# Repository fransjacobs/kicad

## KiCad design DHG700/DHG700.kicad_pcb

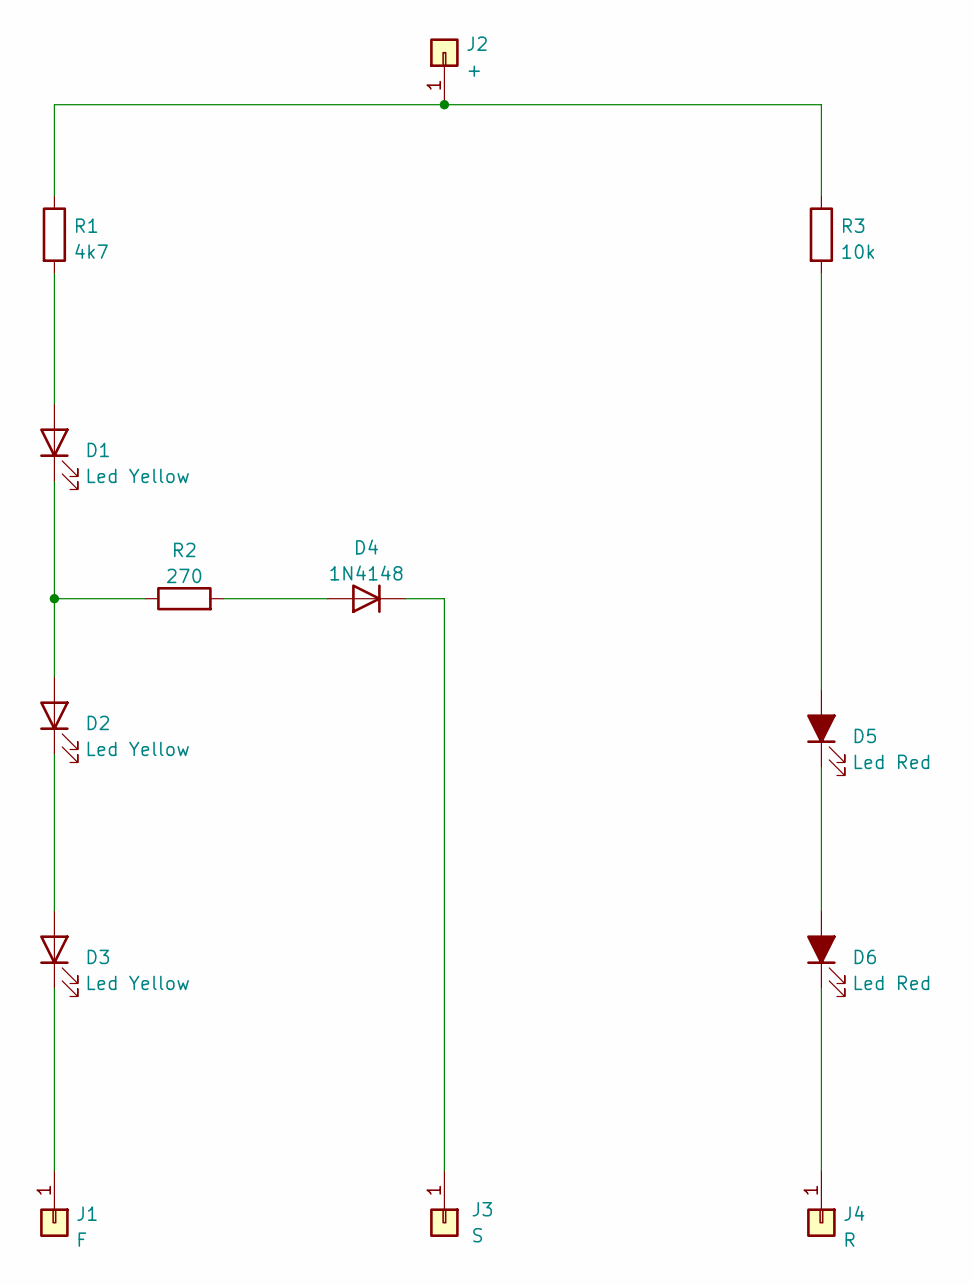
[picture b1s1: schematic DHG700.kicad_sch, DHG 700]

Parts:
D1, D2, D3: Led Yellow; LED_0603_1608Metric
D4: 1N4148; D_DO-35_SOD27_P7.62mm_Horizontal
D5, D6: Led Red; LED_0603_1608Metric
J1: F; SolderWirePad_1x01_SMD_1x2mm
J2: +; SolderWirePad_1x01_SMD_1x2mm
J3: S; SolderWirePad_1x01_SMD_1x2mm
J4: R; SolderWirePad_1x01_SMD_1x2mm
R1: 4k7; R_1206_3216Metric
R2: 270; R_1206_3216Metric
R3: 10k; R_1206_3216Metric

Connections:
unnamed: D1.1 (K), D2.2 (A), R2.1
unnamed: D1.2 (A), R1.2
unnamed: D2.1 (K), D3.2 (A)
unnamed: D3.1 (K), J1.1
unnamed: D4.1 (K), J3.1
unnamed: D4.2 (A), R2.2
unnamed: D5.1 (K), D6.2 (A)
unnamed: D5.2 (A), R3.2
unnamed: D6.1 (K), J4.1
unnamed: J2.1, R1.1, R3.1

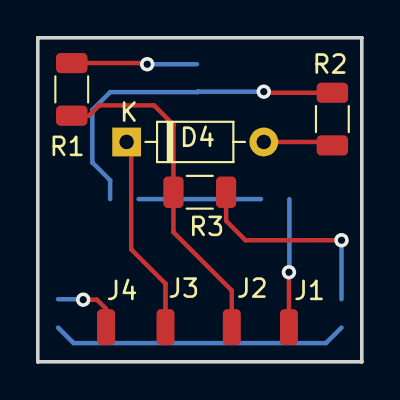
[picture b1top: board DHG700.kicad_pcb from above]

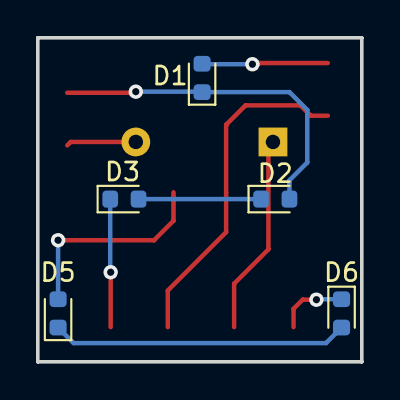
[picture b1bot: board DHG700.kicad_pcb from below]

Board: 2 copper layers, 18.0 x 18.0 mm, 13 parts (5 on the bottom side), 10 nets.

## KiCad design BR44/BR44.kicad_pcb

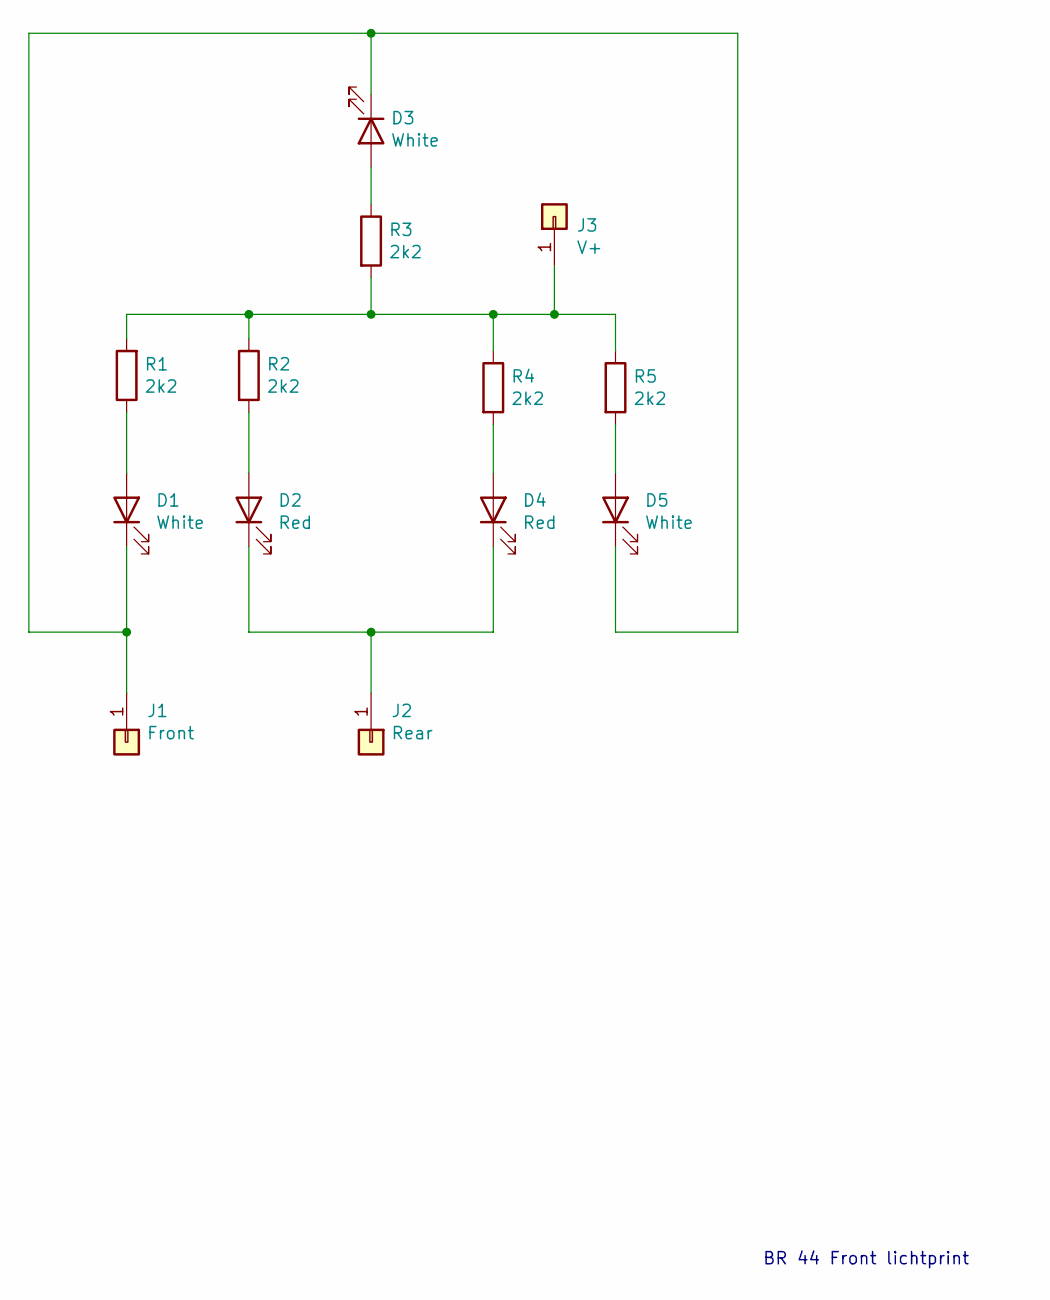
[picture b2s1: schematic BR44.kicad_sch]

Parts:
D1, D3, D5: White; LED_1206_3216Metric_Pad1.42x1.75mm_HandSolder
D2, D4: Red; LED_1206_3216Metric_Pad1.42x1.75mm_HandSolder
J1: Front; TestPoint_Keystone_5019_Minature
J2: Rear; TestPoint_Keystone_5019_Minature
J3: V+; TestPoint_Keystone_5019_Minature
R1, R2, R3, R4, R5: 2k2; R_1206_3216Metric

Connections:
unnamed: D1.1 (K), D3.1 (K), D5.1 (K), J1.1
unnamed: D1.2 (A), R1.1
unnamed: D2.1 (K), D4.1 (K), J2.1
unnamed: D2.2 (A), R2.2
unnamed: D3.2 (A), R3.1
unnamed: D4.2 (A), R4.2
unnamed: D5.2 (A), R5.2
unnamed: J3.1, R1.2, R2.1, R3.2, R4.1, R5.1

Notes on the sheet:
BR 44 Front lichtprint

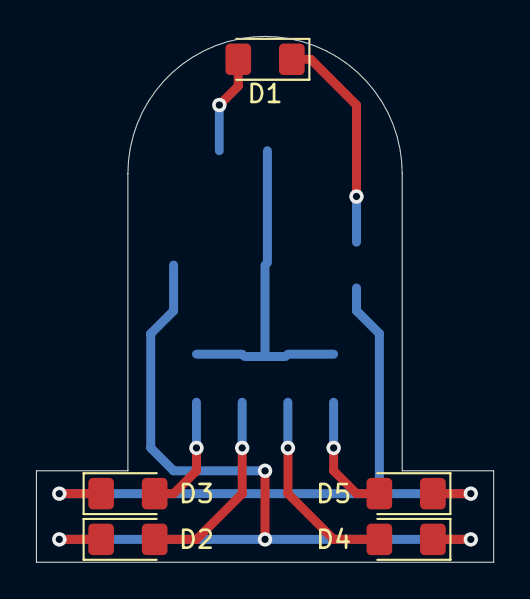
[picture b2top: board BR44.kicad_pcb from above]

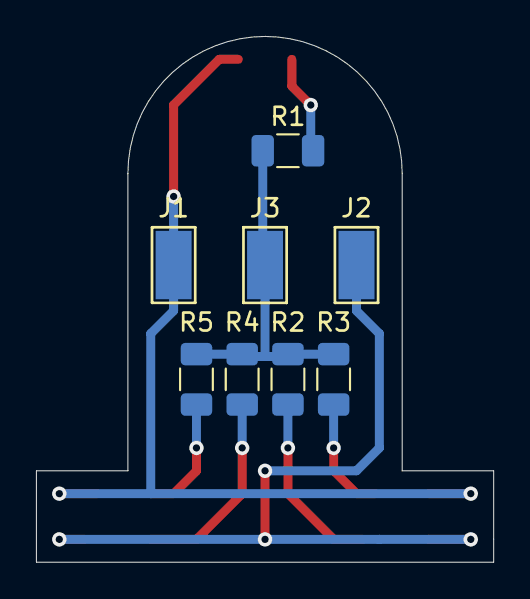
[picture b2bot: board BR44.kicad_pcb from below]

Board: 2 copper layers, 25.4 x 29.2 mm, 13 parts (8 on the bottom side), 8 nets.

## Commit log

2024-03-17 Initial Entry
    My PCB designs for Led light in (old) Marklin locomotives
